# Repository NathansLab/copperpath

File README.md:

# copperpath

Rule-aware routability check, placement helper and grid router for **already-placed KiCad boards**,
written in Rust (parallel with rayon). It reads the board, the net classes (`.kicad_pro`) and the
custom rules (`.kicad_dru`) directly, routes signal nets with exact clearance checks and writes the
result back as ordinary KiCad tracks and vias.

**Status: research prototype.** Tested on KiCad 10 boards (2, 4 and 6 copper layers). Expect
rough edges; see [Limitations](#limitations) and [ROADMAP.md](ROADMAP.md).

At a glance (every command takes `--json`; times on 4 cores):

| | |
|---|---|
| **One-shot routing** | `autoroute`: planes, fanout, signals, pours, thermal fixes and a DRC gate in one call; 2 of 8 PCBench boards fully routed, the others with 1-11 % of their connections left open ([benchmark](#benchmark-pcbench)) |
| **Routing intents per net** | `low_r`, `wide`, `low_l`, `short`, `few_vias`, `quiet`, `first`, `outer`, `z:OHM` (impedance width from the stackup), `pair` (differential pairs); from `--prio`, the project file or the net class name ([intents](#routing-intents-per-net---prio)) |
| **Length matching** | `tune --match 'D[0-7]'`: exact-length accordion meanders, clearance-checked |
| **Native DRC** | the copper checks of `kicad-cli pcb drc` with KiCad's semantics in 7-105 ms instead of 0.7-1.8 s ([DRC](#native-drc-drc)) |
| **For agents** | `status` (overview, suggested intents, next commands) in milliseconds, `explain` (why a net is open), `ripup` + `route --nets` (redo a net in about a second), `netinfo` (R, L, Z0, coupling, bus skew); [a recorded session](docs/agent-session.md) |

## Numbered net compatibility

KiCad 6–9 boards use a numbered net table; KiCad 10 references nets by name. CopperPath now resolves numbered pads, tracks, vias and zones to their real names, validates code/name consistency, and preserves the input net-reference format when routing, applying deltas or creating planes. This fixes routed KiCad-9 output containing invalid quoted numeric net references. Named numeric strings on KiCad-10 boards remain names. Complete compatibility with every older KiCad feature is not implied.

The agentic-eda divider integration independently checks the routed output with KiCad 9 DRC and exports Gerbers; `tests/numbered_nets.rs` covers non-contiguous codes, malformed tables, delta application and roundtrip routing. Existing named-net tests remain required.

## Build

Requires a recent stable Rust toolchain (developed with 1.95).

```bash
cargo build --release          # binary: target/release/copperpath
cargo test --release           # unit tests + routing of the demo board
```

Optional: KiCad 10's `kicad-cli` for the DRC comparison (`route --drc`). It is found via
`--kicad-cli PATH`, else `$KICAD_CLI`, else `kicad-cli` on the `PATH`.

## Quickstart (demo board)

`examples/demo/` holds a small synthetic 4-layer board (25 parts, 24 nets, one rule area, two net
classes, three custom rules), placed but not routed.

```bash
B=target/release/copperpath
$B route --pcb examples/demo/demo.kicad_pcb --out out/demo_routed.kicad_pcb --threads 4
#   [route] 24 nets, 50 connections: 189 segments (604 mm), 29 vias ... 0 opens
$B route --pcb examples/demo/demo.kicad_pcb --out out/demo_routed.kicad_pcb --drc --json
#   {"ok": true, "opens": 0, "vias": 29, "drc": {"new_errors": 0, ...}, ...}
$B check --pcb examples/demo/demo.kicad_pcb --out out/check     # routability report + PNG maps
$B hints --pcb examples/demo/demo.kicad_pcb                      # placement hints
```

Open `out/demo_routed.kicad_pcb` in KiCad. The input board is never modified.

## Commands

All commands take `--pcb BOARD.kicad_pcb`. Common options:

| option | meaning |
|---|---|
| `--cfg config.json` | optional board configuration (see `examples/config.json`) |
| `--board NAME` | entry under `"boards"` in the config (default: the first) |
| `--pro F` / `--dru F` | project / custom rules file (default: next to the board) |
| `--threads N` | worker threads (default: all cores) |
| `--json` | one JSON result object on stdout; logs stay on stderr |
| `--version` | version and git hash |

| command | job |
|---|---|
| `route [--region x0,y0,x1,y1] [--nets PATTERNS] --out OUT.kicad_pcb [--delta-json DELTA.json] [--drc]` | Detailed router (below). Routes every routable net whose pads lie in the region (default: whole board). Appends unlocked tracks/vias to a copy and writes `OUT_route.json`; `--delta-json` writes the added/removed items in nm for the KiCad IPC API ([schema](#change-set-for-the-kicad-ipc-api---delta-json)). `--drc` runs `kicad-cli` on input and output and reports the new violations. |
| `check [--out DIR] [--res 0.25] [--tile 1.0] [--copper locked\|all] [--crop x0,y0,x1,y1 --crop-class C]` | Routability report: via-site maps per net class, region analysis per schematic sheet, what-if ablation (without rule areas, via keepouts, locked copper), global route with congestion per tile and layer, hotspot list. Writes `report.json`, `groute.json`, `congestion.json` and PNG maps. |
| `place --zones zones.json [--init keep\|schematic\|both] [--moves N] [--starts K] [--out DIR]` | Parallel simulated-annealing placement of the movable parts inside zones (see `examples/zones.json`). Writes `place.json`; apply it to a copy with `scripts/apply_place.py`. |
| `tune --match REGEX [--target MM] [--gap MM] [--amax 1] --out OUT` | Length matching: accordion meanders on straight tracks bring every matching net to the target length (default: the longest of them); each bump adds twice its amplitude, the last one the remainder, so the target is met exactly; every new segment keeps the clearances to other nets' copper, holes, rule areas and the board edge. `--json`: length before/after and meanders per net. |
| `thermals --out OUT` | Refills the zones natively and gives every starved thermal pad (fewer than 2 resolved spokes, counted as kicad-cli 10 does: spokes into isolated islands only count when nothing else does, a track from the pad into the fill counts) a short legal stub track into its zone's fill, preferring fill connected to other items. `--json`: starved pads and stubs added. |
| `ripup --nets PATS [--region BOX] [--locked] --out OUT` | Removes the unlocked tracks and vias of the matching nets (with `--locked` the locked ones too), optionally only those touching a region; `--json` lists what was removed per net. With `route --nets` an agent redoes single nets in well under a second. |
| `status [--refill-zones]` | One-call overview for agents, in milliseconds: copper stack, net classes, zones with their selection key, plane nets and candidates, opens per net, native DRC by type, routing intents suggested from the net names (`suggested_prio`: supply rails `wide`, clocks `low_l`, RF `z:50+outer`, analog `quiet`), and the next commands to run (`--json`: `next`). |
| `netinfo [--nets] [--cu-um 35]` | Length, vias, track width and estimated DC resistance (mΩ) and inductance (nH) per net, in milliseconds. See [Routing intents](#routing-intents-per-net---prio). |
| `drc [--refill-zones] [--out report.json]` | Native copper DRC with KiCad's rule names in milliseconds. See [Native DRC](#native-drc-drc). |
| `opens [--region] [--nets] [--max-islands 50]` | Unconnected connections per net, counted from all copper including saved zone fills (no 499-item cap as in kicad-cli). Nets named in `--nets` are counted even if they are plane nets. `--json` lists the islands of each open net (pads per copper component, largest first). |
| `hints [--region] [--nets] [--tol 1.0]` | Pad pairs of a net that are *almost* in one row or column (offset 0.02..tol mm). Each forces a jog between two straight pad exits; align the pads before routing. |
| `stitch --net GND --zones REGEX --plane REGEX [--grid G] --out OUT.kicad_pcb` | Stitching vias for a plane net from the saved zone fills: one via in every fill island of the `--zones` zones (zone name, full match; an unnamed zone matches as `NET@LAYER`, e.g. `GND@In1.Cu`) that has no via or plated hole of the net, optionally a via grid of pitch G per island. A via must lie on a fill of a `--plane` zone of the same net (fully on its copper), keep the DRU/net-class clearance to every other net on every layer (outer layers incl. creepage, last matching rule wins) plus `--margin` (0.05), 0.2 mm to every pad, the hole and edge rules, and stay out of no-via rule areas. Unlocked zones of other nets are ignored (they refill around the via), locked ones are copper. Options: `--via D,DRILL` (default: the net class via), `--min-clr` (floor on the clearance to other nets), `--min-area` (0.3 mm²), `--base B.kicad_pcb` (write the vias into this board instead of the input, e.g. the unfilled original). `--json` lists the vias, the islands without a legal spot (with the nearest blockers of a via there) and the rejection causes. |
| `fanout --net GND --plane REGEX [--reach 6] --out OUT.kicad_pcb` | Connects every open island of a plane net (a copper island with pads that touches no fill of a `--plane` zone) with one short track and a via onto the plane: grid search (0.05 mm, 8 directions) from an SMD pad of the island on its outer layer to the nearest legal via spot within `--reach` mm of track. Track legality as in the router (DRU/net-class clearance incl. outer-layer creepage, rule areas, mask apertures, edge); via legality as in `stitch`. Width: `--width` or the net class / DRU width, inside the pad's own courtyard the width of a DRU `track_width` rule with `A.intersectsCourtyard('REF')` (neck-down). Pads whose own cells are already too close to other copper (in-package creepage) are skipped. Options: `--via D,DRILL`, `--margin`, `--min-clr`, `--islands opens.json` (only islands listed by `opens --json`), `--base`. `--json` lists per island the pad used, track length and via, or why each pad failed and the nearest blockers (`net`, `kind`, `fp`, `layer`, `dist_mm`, `need_mm`, `locked`, `at`: the copper closest to violating its clearance, i.e. what to move). The search runs in 8 directions, so 45-degree tracks to a via spot are tried as well. |
| `nudge (--parts R5,R7 \| --spec moves.json \| --auto) [--range 1] [--step 0.05] [--rots 0,90] --out OUT.kicad_pcb [--dry-run]` | Local placement optimisation by real routing: moves a few small parts (translation on a grid, rotation about the footprint origin, side kept) until their nets route, see [Nudge](#nudge-local-placement-by-real-routing). Writes the moved footprints and the new copper to a copy and `OUT_nudge.json`. |
| `render [--roi x0,y0,x1,y1] --out roi.png` | PNG of a board region for AI agents and humans, native rasteriser (about 0.05 s per image). See [Rendering](#rendering-render). |
| `autoroute --out OUT.kicad_pcb [--time 600] [--planes In1.Cu=GND]` | Placed board to routed board in one command: plane zones, plane fanout, signal routing, rip-up of blockers, stitching, quality gate. See [One-shot routing](#one-shot-routing-autoroute). |
| `explain [--net N] [--pad REF.PIN] [--explain-img DIR]` | Why connections are open: reason, widest corridor, blockers, ROI image. See [Explaining failures](#explaining-failures-explain). |
| `plane list\|report\|fill\|create\|adjust` | Plane zones: detection, native zone filler, report (islands, unconnected pads, necks, stitching coverage), zone creation with HV cut-back, grow/merge. See [Planes](#planes-plane). |
| `pads` | Pad world positions, sizes and nets (tab separated). |
| `netclass` | net → net class table (tab separated). |

`--nets` takes comma-separated wildcards (`*`, `?`), e.g. `--nets "/Driver/*,+5V"`.

### Route options

| option | default | meaning |
|---|---|---|
| `--res` | 0.05 | grid resolution in mm; `auto`: 0.1 mm when every routed net has at least 0.2 mm clearance and width and no pad pitch is under 0.5 mm (4x fewer cells) |
| `--via-cost` | 30 | via cost (in grid steps) |
| `--bend-cost` / `--bend90` | 4 / 1.4 | cost of a 45° bend / factor for 90° bends |
| `--hweight` | 1.02 | A\* heuristic weight (>1: faster, less optimal) |
| `--max-expand` | 4e6 | node budget per search (at least half the nodes of the net's window) |
| `--iters` | 25 | negotiation iterations |
| `--job-margin` | 6 | per-net search window margin in mm |
| `--time-limit S` | | stop negotiating in time and write the best iteration so far (conflicting nets ripped and rerouted, or left as failed); SIGTERM / Ctrl+C (Ctrl+Break on Windows) do the same at once. `--json` reports `stopped` (`time-limit`, `signal`, `cancel`) and `hotspots` (net, conflict cells, location, layer) |
| `--cancel-file PATH` | | stop like `--time-limit` as soon as this file exists (checked once per second); a cancel path that also works on Windows, where a GUI can only kill the process otherwise. The file should not exist at the start |
| `--cancel-on-stdin-eof` | | stop like `--time-limit` when stdin is closed, e.g. because the calling plugin or KiCad ended |
| `--progress-json` | | machine-readable progress on stderr, one JSON object per line ([events](#progress-events---progress-json)) |
| `--stall-iters` | 3 | stop negotiating after this many iterations without fewer conflict cells, then rip up and reroute the conflicting nets |
| `--stall-gain` | 0 | an iteration counts as progress only if it cuts the best conflict count by this fraction (0.1 = 10 %); stops plateaus early |
| `--no-fallback` | off | skip the cleanup fallback ladder (two more full routes when the exact check drops nets); the dropped nets stay open and are reported |
| `--par-nets` | 1 | 1 = nets whose windows cannot interact route in parallel (same result as serial); N > 1 = blocks of N nets against one snapshot (experimental) |
| `--par-conn` | 1 | experimental: parallel connection searches inside a multi-pin net (0 = all threads); slower on the benchmark boards so far |
| `--no-stubs` / `--no-clean` | | disable straight pad exits / the cleanup |
| `--stub-ext` / `--stub-ext-long` | 0.6 / 0.6 | exit stub length beyond the pad (mm) |
| `--own-pad-cost` / `--stub-side-cost` | 40 / 20 | cost of crossing own pads / of side exits on long pads |
| `--yield-pours PATTERNS` | | locked pours (zone name wildcards) that do not block (KiCad refills them); also `yield_pours` in the config |
| `--ignore-unlocked` | | the router does not see unlocked tracks, vias and zones of the input, but they stay in the output (route never removes copper), so new copper can overlap or short them. Only for experiments where the old copper is deleted afterwards; rip up instead (see below) |
| `--reroute-blockers` | | after routing, for each net still open: a coarse search (0.1 mm, all layers) in which unlocked tracks/vias of other nets are passable at a high cost finds the cheapest corridor; the unlocked copper on it is ripped and the net is routed again together with the ripped nets (negotiated as usual). A try is kept only if the net gets fewer opens and no ripped net and no other net ends up with more opens; otherwise it is rolled back. Locked copper, pads, rule areas and the edge are never moved. `--json`: `reroute` = per net `ripped_nets`, `ripped_items`, `accepted`, opens before/after, `reason` |
| `--max-ripped N` / `--max-targets N` | 3 / 10 | blocking nets ripped per try / open nets tried |
| `--dbg-net NAME` | | verbose trace of one net |

## Rendering (`render`)

One PNG of a region with every copper layer colour-coded and semi-transparent (KiCad colours,
B.Cu at the bottom, F.Cu on top), so an AI agent can *look* at a placement or routing problem
instead of reading coordinates. Native Rust, no Python or matplotlib.

```bash
B=target/release/copperpath
# region around a part, labels, ratsnest of the open connections, DRC markers
$B render --pcb board.kicad_pcb --roi 110,105,135,125 --labels --opens --drc drc.json --out roi.png
# one small image per copper layer (small multiples)
$B render --pcb board.kicad_pcb --per-layer --layers F,In1,In2,B --labels --out sheet.png
# one net highlighted, all other copper grey
$B render --pcb board.kicad_pcb --hl-net GND --fills --out gnd.png
```

| option | default | meaning |
|---|---|---|
| `--roi x0,y0,x1,y1` | board + 1 mm | region in board mm |
| `--px N` | 1200 | image width in pixels (height from the aspect ratio) |
| `--layers F,In1,..,B` | all | copper layers to draw (`F.Cu` style names work too) |
| `--nets REGEX` / `--hl-net NAME` | | only these nets / this net in colour, everything else grey |
| `--fills` | off | saved zone fills (`filled_polygon`), lighter than tracks |
| `--labels` | off | `REF.PIN` and net name on every pad in the region (largest pads first, never overlapping; a label that does not fit is moved beside the pad or dropped), net names on long tracks |
| `--opens` | off | ratsnest: one white line per open connection (minimum spanning tree over the copper islands of each net, closest pad pair) |
| `--drc FILE` | | markers from a `kicad-cli pcb drc --format json` report: red X for errors, yellow for warnings, dashed line for unconnected items |
| `--courtyards` | off | courtyard outlines |
| `--halo-min D` | 1.0 | nets whose outer-layer clearance (incl. creepage) to another net in the region is at least D mm get a hatched halo of that width (HV creepage zones); 0 = off |
| `--per-layer` | off | one tile per layer in a grid |

Always drawn: board outline, rule areas (orange hatch), vias and drill holes, a millimetre grid
with coordinates along the top and left edge, a scale bar and a legend. `--json` returns the
image size, the region, `px_per_mm`, the number of labels and the open connections in the region
(`ratsnest`: net, both pads, end points, length).

## Planes (`plane`)

Plane nets (GND, supply rails) get zones instead of tracks. `plane` creates and edits those
zones, fills them natively and reports how well they connect, without `kicad-cli`.

```bash
B=target/release/copperpath
$B plane list --pcb board.kicad_pcb                       # plane/pour nets and power-like candidates
$B plane create --pcb board.kicad_pcb --net GND --layer In1.Cu --out step1.kicad_pcb
$B plane create --pcb board.kicad_pcb --net +3V3 --layer In2.Cu --region 100,100,140,150 \
   --hv "HV_.*" --creepage 3 --out step1.kicad_pcb       # cut back 3 mm from the HV nets
$B plane adjust --pcb step1.kicad_pcb --zone "cp_plane_*" --grow max --merge --out step2.kicad_pcb
$B plane report --pcb step2.kicad_pcb --net GND --json --png gnd.png
$B plane fill --pcb step2.kicad_pcb --out filled.kicad_pcb  # write native fills (filled_polygon)
```

| subcommand | job |
|---|---|
| `list [--min-pads 4]` | nets with copper zones (`plane`: a zone on an inner layer, `pour`: any zone) and power-like nets (`GND*`, `+*`, `VCC*`, `VDD*`, `VBAT*`, ...) with at least N pads and no zone (`candidate`), with net class, pad count and zones. |
| `create --net N --layer L [--region box] [--hv REGEX --creepage D] [--priority P] [--name NAME] --out F` | one zone of net N on layer L over the board (or the region): the free area of the layer, i.e. inside the board, outside pour keep-outs, rule clearance (+ `--margin`) away from zones of other nets, and `--creepage` mm away from all copper of the `--hv` nets on that layer. Parts narrower than `--min-neck` (1.0 mm) and outlines under `--min-area` (4 mm²) are dropped. The outline is cut back where HV copper reaches it; HV copper inside the plane gets a pour keep-out rule area (`NAME_hvK`, copper pour not allowed, tracks and vias allowed). Name `cp_plane_<net>_<layer>`; a re-run replaces its own zone and keep-outs. Clearance from the net class, `--min-width` (0.25) as minimum thickness, thermal reliefs; KiCad fills it. |
| `adjust --zone NAME [--grow D\|max] [--hv REGEX --creepage D] [--merge] --out F` | edits existing zones (name wildcards): grow the outline by up to D mm (`max`: the whole free area connected to it) into the free area as above, cut it back from HV copper, `--merge` joins the selected zones of one net and layer set into one outline. Only the polygon changes; every other zone setting is kept, saved fills are dropped. |
| `report [--net N] [--stitch-radius 5] [--necks 5] [--png F [--roi] [--labels]]` | native fill of every zone of the net (default: all nets with zones), then per zone and layer: outline and fill area, lost area (%), islands, isolated islands (no copper of the net: KiCad removes them), connected islands without a via, share of the largest island, stitching coverage (fill within `--stitch-radius` mm of a via or plated hole, %), narrowest neck; per net: copper components through all copper (tracks, vias, pads, native fills), unconnected pads (not in the largest component), the narrowest necks with position. `--png` renders the net with its native fill, ratsnest and the necks as markers. |
| `fill [--net N] --out F` | writes the native fill as `filled_polygon` into a copy (fractured polygons like KiCad's). |

Native filler: raster of the zone's layer (`--fill-res`, 0.1 mm), KiCad's recipe: the area where
a disk of half the minimum width (`--min-width`, 0.25 mm) fits (outline, board edge clearance,
clearance + half width to foreign copper, holes, pour keep-outs, zones of other nets with a higher
priority) grown again by half the width. Pads of the net connect solidly (thermal spokes are not
modelled), isolated islands are dropped. On the demo board with a GND plane on In2 the filled
area matches KiCad's within 0.2 %; 0.05 s per zone layer. A neck is where two parts of an island
that both hold copper of the net meet (widest-path tree over the distance to the fill edge).

`--native-fill` on `fanout`, `stitch`, `opens` and `render` fills all copper zones natively first
(instead of the saved fills), so the plane loop needs no kicad-cli refill.

## One-shot routing (`autoroute`)

```bash
$B autoroute --pcb placed.kicad_pcb --planes In1.Cu=GND,In4.Cu=+3V3 --time 600 --drc    --explain-img why/ --out routed.kicad_pcb --json
```

Stages (each writes its board to `OUT_stages/`, the input is never modified):

1. **planes**: `--planes LAYER=NET[+NET],...` creates the missing plane zones (`plane create`).
   Plane nets = the nets of `--plane-nets A,B`, of `--planes` and every net with a copper zone
   on an inner layer; they are not routed as signals. Nets with outer pours only (two-layer
   boards) are pour nets, see stage 3c.
2. **fanout**: every open island of each plane net gets a track + via onto its plane
   (`fanout --native-fill --plane-only`; the plane = its zones on inner layers; outer pours of
   the net do not join pads here, so tracks routed later cannot strand a pad cut off a pour).
3. **route**: the negotiated router for all other nets with `--time-limit` = the time left minus
   a reserve, plus `--reroute-blockers` (off with `--no-reroute`). Signal tracks stay off inner
   layers whose plane zones cover at least half the board (`--signal-layers auto`, the default;
   `all` or a layer list to override); vias still pass through the planes.
   `--second-pass` retries the nets left open with `--job-margin 20 --max-expand 2e7` in the
   time left.
3c. **pours**: the pour nets are routed after the signals: the zones are filled natively and
   the router only joins what the fill leaves apart, starting on the fill (no signal is
   ripped); new tracks can cut another pour, so fill and route repeat up to 3 times. Plane
   nets with pads the plane and the fanout could not join (dense through-hole pins between
   which the plane cannot pour) are routed here too, on the signal layers.
3e. **polish**: when a quarter of the budget is left (small boards finish early), the nets
   still open get a rip-up-and-reroute round on the filled board (up to 20 targets); the result
   is kept only when the board has fewer opens (rf_siggen 16 -> 14, rxadc_14 5 -> 4; off with
   `--no-polish`).
3d. **thermals**: pads whose thermal relief resolves to fewer than 2 spokes (`starved_thermal`
   in kicad-cli) get a short stub track from the pad centre into connected fill of their zone,
   which kicad-cli counts as a spoke (`thermals`; off with `--no-thermals`). On the routed
   sizif128 board: kicad-cli `starved_thermal` 17 -> 7, no new violations.
4. **stitch**: stitching vias for outer pours of the plane nets onto their inner planes
   (`--stitch-grid G` adds a grid; off with `--no-stitch`).
5. **gate**: opens of every net counted with native fills; with `--drc` KiCad DRC of the result
   against the input; if a stage added DRC errors, the latest stage without new errors is
   written, and if none is clean nothing is written (exit 1, `--allow-drc` writes anyway).

`--json`: `opens_before`, `opens`, `open_nets`, `plane_nets`, `within_budget` and per stage
`s`, `opens`, `note`, `out` and details (fanout islands, route `open_nets`, DRC deltas). With
`--explain` / `--explain-img DIR` the open connections of the result are explained (see
[Explaining failures](#explaining-failures-explain)). Routed copper that fails the exact
clearance check is never written: the failing segments and whatever then dangles are removed,
the rest of the net stays, and the connection is left open (`aes.exact_dropped` counts the nets).

Synthetic stress board (`scripts/make_stress.py --parts 800`: 798 footprints, 6 layers, 515
signal nets, GND/+3V3 zones on In1/In4; 4 cores, 8 GB): 1331 to 174 opens in 75 s (fanout 3 s,
route 70 s). Before skipping the fallback ladder for pure search failures (#54) the route stage
took 217 s. The 134 signal opens left are router search failures where `explain` finds a legal
corridor (#87), the 40 plane opens are pads whose fanout found no via spot.

Demo board, `--planes In1.Cu=GND`: 50 to 0 opens in 8 s (gate with KiCad DRC +16 s, 0 new
errors; KiCad warns about dangling GND vias until the plane is refilled).

## Routing intents per net (`--prio`)

`route` and `autoroute` take a routing intent per net (`--prio NET=PROFILE,...`, wildcards, or
`net_prio` in the config). It scales the router's costs for that net and its track width, and
nets marked `first` are routed before the others:

| profile | effect | use for |
|---|---|---|
| `low_r` | twice the class width (pads keep the neck-down), vias cost 2x, first | high current; costs completion on dense boards (icehat, `--time 10`: 26 instead of 18 open), where `wide` is the gentler choice |
| `low_l` | vias cost 3x, bends and the wrong layer direction cheap (direct path), first | clocks, gate drives, decoupling loops |
| `short` | bends and the wrong layer direction cheap | sense lines, short analog paths |
| `few_vias` | vias cost 4x | signals that should stay on one layer |
| `wide` | 1.5x the class width | supply rails, moderate current (what `status` suggests for rails) |
| `quiet` | cells within 0.5 mm beyond the clearance of other nets' copper (fixed and routed) cost more | sensitive analog, clocks next to aggressors |
| `first` | routed before the other nets | the nets that matter most |
| `pair` | differential pair: the negative net (`_N`, `-`, `DM`) follows the positive one (`_P`, `+`, `DP`, routed first) at the class `diff_pair_gap` (else the clearance), both at `diff_pair_width` if set; the follower skips the pull-tight | USB, LVDS, MIPI: `USB_D*=pair` |
| `outer` | tracks only on F.Cu and B.Cu (vias still pass the inner layers) | with `z:` so the width holds everywhere, nets to probe or rework |
| `z:OHM` | track width for that single-ended impedance on the outer layers, from the board stackup (microstrip, Hammerstad-Jensen; without a stackup: FR4 4.5, 35 µm, 0.2 mm prepreg on multilayer boards, 1.51 mm on two layers) | RF, USB/LVDS lines, clocks: `RF_OUT=z:50` |
| `via:X` `bend:X` `dir:X` `width:X` `iso:X` | the multipliers themselves, `iso` the soft spacing in mm | fine tuning |

Pairs whose names do not mark the polarity (`Net-(J1-Pad3)`) are named explicitly:
`--pairs 'POS=NEG;POS2=NEG2'` or `"pairs": [["POS", "NEG"]]` in the config or the project's
`copperpath` block; they need no `pair` intent.

A differential pair without and with `pair` (`USB_D*=pair`; `netinfo --near 0.4`: USB_D- runs
within 0.4 mm of USB_D+ for 1.7 mm without, 28 mm of its 34 mm with the intent; DRC clean):

`tune --match 'PWM_.*|ADC[12]'` then matches such a group to its longest net (demo: skew
4.97 mm -> 0, DRC clean; left before, right after):

`netinfo --match 'D[0-7];A[0-9]+'` adds the length skew per group of nets (shortest, longest,
`skew_mm`) for buses that need length matching. `netinfo` reports `z0_ohm`, the microstrip impedance of a net's narrowest outer-layer track
(demo, `CLK=z:50`: 0.341 mm, 50.0 Ω). `netinfo` also reports `coupled_mm`, the track length running closer than `--near` (0.5 mm, edge
to edge) to another net's copper on the same layer: on the demo, `CLK=quiet` cuts it from 11.2 to
0.1 mm at the same length.

Profiles combine with `+` (`CLK=low_l+wide`). A key `class:PATTERN` applies to the nets of the
matching net classes (`--prio 'class:Power=low_r'`). The intents can live in the KiCad project
next to its net classes, as a `copperpath` block in the `.kicad_pro` (KiCad keeps unknown keys):

```json
"copperpath": { "net_prio": { "class:Power": "low_r", "CLK*": "low_l", "SW": { "via": 3, "width": 2 } } }
```

The net class itself can carry the intent: a KiCad net class named after a profile (`quiet`,
`low_l+wide`) or ending with one in brackets (`Power [low_r]`) gives its nets that intent, so it
shows up in KiCad's net class list without extra configuration.

Order: `--prio` first, then `net_prio` of `--cfg`, then the project block, then the net class
name; the first match wins. `netinfo` reports the result per net: length, vias,
width and rough DC resistance (copper 35 µm, `--cu-um`) and partial inductance (Grover formula
for the total length plus about 1.3 nH per 1.6 mm via). Demo board, `route` without and with
`--prio '+5V=low_r,CLK=low_l,ADC1=few_vias'` (both DRC-clean):

| net | without | with |
|---|---|---|
| +5V (`low_r`) | 0.4 mm, 51.2 mm, 64.5 mΩ | 0.8 mm, 50.4 mm, **32.6 mΩ** |
| CLK (`low_l`) | 22.1 mm, 2 vias, 27.1 nH | 22.4 mm, **0 vias, 24.9 nH** |
| ADC1 (`few_vias`) | 17.8 mm, 3 vias | 18.4 mm, **0 vias** |

Left without, right with `--prio '+5V=low_r,CLK=low_l,ADC1=few_vias'` (`render --nets
'\+5V|CLK|ADC1' --labels`: only these nets' copper, F.Cu red, B.Cu blue).

## Native DRC (`drc`)

```bash
$B drc --pcb routed.kicad_pcb --refill-zones --out report.json --json
```

The copper checks of `kicad-cli pcb drc`, on copperpath's model: `clearance`, `shorting_items`,
`tracks_crossing`, `hole_clearance`, `hole_to_hole`, `copper_edge_clearance`, `track_width`,
`via_diameter`, `annular_width`, `drill_out_of_range`, `starved_thermal` (with `--refill-zones`, resolved as kicad-cli 10: spokes per fill polygon,
spokes into single-connection islands ignored while the pad has another spoke or a track into
the fill) and
`unconnected_items`, with KiCad's semantics (net classes, DRU and pad clearances, the 0.0005 mm
epsilon, one collision per net pair, collisions only between nets with pads). `--refill-zones`
fills the zones natively first (like kicad-cli's flag, with thermal reliefs), otherwise the
saved fills count. `--out` writes a report in kicad-cli's JSON layout.

Checked against kicad-cli 10.0.7 on six routed PCBench boards (see the benchmark below) and on
synthetic boards:

- with the zone fills saved by KiCad: the same violations per type and the same unconnected
  items per net, in 10-40 ms instead of 0.8-0.9 s per board;
- with `--refill-zones` (native filler, 0.05 mm raster by default, `--fill-res`): the same
  copper violations, unconnected items within 1-2 of kicad-cli's and `starved_thermal` within 2
  (the filler rasterises necks that are exactly the minimum width), 0.1-1.2 s instead of 1-2 s.

`route`, `nudge` and `autoroute` take `--drc native` for their DRC gate: the same comparison
against the input as `--drc` (kicad-cli), with the input's rules for both boards, in
milliseconds. Pads with the same number in one footprint count as one terminal (as in KiCad).
Board setup minimums missing from the project take KiCad's defaults (0.5 mm via, 0.1 mm annular
ring, 0.3 mm hole), for the router as well. Not covered: silk, courtyard, solder mask, footprint
library checks, and copper islands without pads (KiCad counts floating
tracks as unconnected items). Use it as the fast check while iterating and kicad-cli for
sign-off.

## Explaining failures (`explain`)

Every failure comes with a one-line reason for humans and agents, and optionally a small image.
`--explain` adds them to the JSON of `route`, `fanout`, `stitch` and `plane report`;
`--explain-img DIR` also writes one ROI image per failure (the net highlighted, its ratsnest,
labels, rule areas, HV halos, the bottleneck as a red marker and the blockers as yellow markers,
scale bar). `copperpath explain` analyses the open connections of one net (or one pad) directly.

```bash
$B explain --pcb routed.kicad_pcb --net /Driver/PWM_A --pad U3.7 --explain-img why/ --json
$B route --pcb board.kicad_pcb --out routed.kicad_pcb --explain-img why/ --json
$B fanout --pcb board.kicad_pcb --net GND --plane "GND_In.*" --native-fill --explain --out f.kicad_pcb
```

For an open connection (the two closest pads of two copper islands of the net) the legal
track-centre area is rasterised in a window around both pads (all allowed layers, vias where one
fits; clearances from the DRU/net classes incl. creepage, rule areas, mask apertures, board edge):

| `kind` | meaning |
|---|---|
| `congestion` | a corridor at the net's minimum width exists: the router ran out of iterations or budget (try `--reroute-blockers`, `--iters`, a region route) |
| `routed-copper` | only unlocked tracks/vias of other nets block it; `rip_nets` lists the rip-up candidates |
| `neck-down` | only the minimum width gets through, but the router allows it within 1.5 mm of the own pads only; `at` is where the net width does not fit |
| `too-narrow` | fixed obstacles leave at most `corridor_mm` of track (< `need_mm`); `at`/`layer` is the bottleneck, `blockers` what to move |
| `enclosed` | no legal path even for a zero-width track; `at` is the reachable point closest to the target |

Example reason: `widest free corridor fits a 0.05 mm track < 0.20 mm needed at (19.62, 14.78)
F.Cu: blocked by locked track SIG on F.Cu (0.20 mm away, needs 0.20)`. Options: `--explain-max`
(20), `--explain-px` (900). About 0.05 s per connection including the image.

### Existing copper, "route the rest" and rip-up

`route` never removes or moves existing copper: every track, via and zone of the input stays in
the output with its UUID, and the delta's `remove` list is empty. Existing tracks and vias of a
net count as connectivity for that net and as obstacles for all other nets, locked or not
(unlocked zones yield, KiCad refills them). So routing
again after manual work only adds the missing connections ("route the rest"); a separate
`--lock-all-existing` option is not needed, it is the default. New copper is written unlocked
with fresh UUIDs (seeded from the input board, so a second run never repeats the first run's
UUIDs).

To redo nets, rip them up first: delete their unlocked tracks and vias (in KiCad, or with the
plugin's **Rip up selected nets**), then route them with `--nets`.

## How routing works

- **Model.** Grid of 0.05 mm cells on every copper layer of the board, 8 directions plus through
  vias. Legality is exact at cell centres: a track centre may sit in a cell when its half width
  plus the clearance from the net-pair matrix (net classes + DRU rules, outer/inner layer
  conditions, hole clearances, rule areas, board edge) keeps it off every foreign object; touching
  the clearance exactly is legal, as in KiCad's DRC. Solder mask apertures on the outer layers
  (F/B.Mask graphics, pad mask expansions from the pad, footprint or `pad_to_mask_clearance`) admit
  only the nets of the pads and locked zones inside them, so no copper of another net is exposed
  next to a pad (KiCad `solder_mask_bridge`). Tracks use the DRU/net-class optimal width; within
  1.5 mm of own pads the minimum width is allowed (neck-down for fine pitch). The grid is shifted
  by less than one cell so that the axes of the tightest pin rows lie on cell centres (a 0.2 mm
  track between 0.2 mm pads at 0.4 mm pitch fits only exactly on the pad axis).
- **Search.** Windowed multi-target A\* per net; nets are routed in parallel per iteration. A
  connection starts or ends at a pad (through its exit stub) or on any existing track or via of
  the same copper component, so a boxed-in pad still joins through its own via.
- **Negotiation.** PathFinder-style congestion costs (present × occupancy + history), stall
  detection, then rip-up of the most conflicted nets and a hard reroute.
- **Verification.** All routed copper is checked exactly against fixed objects and other nets
  before writing; a failed check is reported (`aes.exact_fail`), never silently written.

### Aesthetics rules (on by default)

- **Straight pad exits.** Each pad gets precomputed exit stubs per layer and pad axis, running from
  the pad centre along the axis to half extent + 0.6 mm. Long pads (aspect ≥ 1.2) exit along the
  long axis whenever that is legal. Where no full stub fits, a short stub (0.12–0.4 mm beyond the
  pad) is used and counted (`aes.short_stubs`).
- **45° only.** Tracks are octilinear; no turns sharper than 90°; 45° bends are cheaper than 90°.
  A final polish replaces slightly off-angle segments by small axis jogs (`aes.axis_jogs`).
- **Exact cleanup.** Stub alignment, octilinear pull-tight with 1–3 segment links, jog merge,
  stub-end and junction sliding (never into pads), via slide onto the stub axis, 45° mitering of
  90° corners, removal of tiny junction legs. Every change is re-checked against the rules and the
  other nets, so the cleanup cannot add DRC errors. Kept 90° corners are reported by cause
  (`aes.kept90_by_cause`).
- **Fallback ladder.** If the cleanup costs completeness (a net loses a connection), the router
  reruns without sliding (`no-slide`), then without cleanup (`no-clean`). The level used is in
  `aes.cleanup_level`.

## Nudge: local placement by real routing

A pad that the router cannot reach is often fixed by moving a resistor half a millimetre or turning
it. `nudge` searches such moves and judges every candidate by routing it for real:

```sh
# move R5 and C7 by up to 1 mm on a 0.05 mm grid, also try them turned by 90 degrees
copperpath nudge --pcb board.kicad_pcb --parts R5,C7 --range 1 --step 0.05 --rots 0,90 \
  --out nudged.kicad_pcb --json
# only report the best moves
copperpath nudge --pcb board.kicad_pcb --parts R5 --dry-run --json
# pick the parts automatically: unlocked 2-pad SMD parts within 3 mm of an open connection
copperpath nudge --pcb board.kicad_pcb --region 40,20,60,35 --auto --auto-dist 3 --auto-max 4 \
  --out nudged.kicad_pcb
# joint moves: neighbouring small passives within 2 mm may be pushed up to 1.5 mm out of the way;
# open connections from the parts up to 40 mm away are routed too; LV signal tracks may be ripped
copperpath nudge --pcb board.kicad_pcb --parts C316 --range 2 --rots 0,90,180,270 --push 2 \
  --push-range 1.5 --reach 40 --rip-classes "LV_SIG*" --exclude-nets "GND*" --explain-img why/ --out n.kicad_pcb
# full move spec (per part ranges, rotations, keep-in polygon; see examples/nudge.json)
copperpath nudge --pcb board.kicad_pcb --spec examples/nudge.json --time-limit 30 --out nudged.kicad_pcb
```

- **Move space.** Per part an x/y offset range on a grid (`dx`, `dy`, `step`; default `--range`
  ±1 mm, `--step` 0.05 mm) and a list of rotations (`rot` absolute or `drot` relative, default
  `--rots 0`), optionally a `keepin` polygon. The side stays. Locked parts are refused unless
  `--move-locked`.
- **Hard rules.** Every candidate passes the placement checker of `place` first: pad clearance from
  the DRU/net-class matrix (outer layers incl. creepage), mounting-hole keepouts, via-to-pad gap,
  courtyard overlap, board edge clearance, footprint rule areas and the keep-in. A candidate may
  not have more violations than the start placement.
- **Real routing.** The nets to route are the nets of the movable parts plus the nets open in the
  region (or `--nets`). Their unlocked tracks and vias inside the region are ripped once
  (`--rip region`; `attached` rips only the copper connected to the movable parts, `none` keeps
  everything), then every candidate is routed by the detailed router inside the region (default:
  the parts' move envelope + `--margin` 2 mm).
- **Joint moves.** With several parts, candidates also shift all scanned parts together. With
  `--push R` the small passives (2 SMD pads) within R mm of a part's move envelope join as push
  parts (range `--push-range`, rotation kept): a move whose courtyard or pads collide with a
  movable part pushes that part along the move (or away after a pure rotation) until it is
  clear, up to two levels deep; the repaired candidate is checked and routed like any other
  (`pushed` counts them). Connectors, ICs and parts not allowed to move are never pushed.
- **More nets.** `--reach D`: an open connection that starts in the move envelope and ends
  within D mm is routed too (the region grows to its far end; `log[0].reach` lists them).
  `--rip-classes PATS`: unlocked copper of nets of these classes inside the region is ripped and
  rerouted as well (blocking nets). `--exclude-nets PATS`: never routed or ripped (e.g. pours).
- **Score.** Opens first, then cost = track length + `via_w` (2 mm) per via + `move_w` (2 per mm)
  × moved distance + `rot_w` (0.5) per turned part. The result is written only if it has fewer
  opens than the board as it is (`improved`).
- **Search.** A coarse scan of each part's move space (`--coarse` 9 points per axis × rotations),
  then a pattern search around the best (step halving down to the grid step), in rounds over all
  parts until nothing improves, `--time-limit` (60 s) or `--max-cands`. Candidates of a step are
  evaluated in parallel.
- **Speed.** The board is cropped once to the region plus the router's job margin (all copper of
  the routed nets stays, so their connectivity is exact). The blocker maps of everything that
  does not move are built once; a candidate only stamps the moving pads into copies of them and
  routes without the exact cleanup; the winner is routed again with the cleanup. On a 6-layer
  board with 845 footprints, two parts and three nets (32 ripped items, GND among them) a
  candidate costs about 11 ms wall time on 4 threads (≈ 0.8 ms model, 7 ms maps, 33 ms
  search per thread); 330 candidates in 4 s.

`--json` / `OUT_nudge.json`: `moves` (per part `from`/`to` as x, y, rotation and `dx`, `dy`,
`drot`), `nets` (opens before/after per net), `score` (opens, length, vias, moved mm, rotated
parts, cost), `opens_before`, `opens` (counted again on the written board), `candidates`,
`infeasible`, `infeasible_reasons` (most frequent rule hits of the rejected candidates: courtyard
overlap with which part, pad too close to which item of which net, outline, keep-in, edge, rule
area; with an example position), `pushed`, per failed net `reason` (why the router gave up) and
`components` (pins per unconnected copper component), `route_ms_per_candidate`, `search_s`, `stopped`, `log` (search phases and a time
profile), `ripped_items`, `region`, `warnings` (e.g. zones without saved fill: refill the board
first, otherwise pour connectivity is unknown and the opens are wrong). `--explain-img DIR` renders
a `render` ROI image (labels, courtyards, ratsnest) per failed net and for the top blocking
reasons and adds its path as `img`. `--drc` compares kicad-cli DRC before/after as in `route`.

Limits: no side flip; copper graphics inside a moved footprint are not moved in the routing model
(the written board moves them, KiCad keeps them local); the saved zone fills are not refilled
(run the zone filler in KiCad afterwards).

`hints` finds the placement-side cause of many ugly jogs: two pads of a net that are almost, but not
exactly, aligned. Fix those in the placement and the exits connect with one straight track.

## Board configuration

`--cfg` is optional. `examples/config.json` documents the keys: nets/classes to skip, plane nets,
footprints whose courtyard forbids vias, allowed layers per net class, preferred layer directions
for the global router, mounting-hole pattern. Keys may be per board under `"boards"`.

## Using copperpath from scripts/AI agents

Every command accepts `--json`. It then prints exactly **one JSON object** to stdout; human-readable
logs go to stderr. Exit codes: `0` success, `1` error in a known command (bad file, bad option,
kicad-cli failure), `2` unknown or missing command.

Common fields: `ok`, `command`, `version`, `threads`, `total_s`, `warnings`. On error:
`{"ok": false, "command": ..., "error": "...", "version": ...}`.

A short loop for an agent (times on the PCBench icehat board, 4 cores; a complete recorded
session with every command and its result: [docs/agent-session.md](docs/agent-session.md)):

| step | command | time |
|---|---|---|
| look | `status --json` (opens, DRC, classes, zones, `suggested_prio`, `next` commands) | 14 ms |
| route | `autoroute --out r.kicad_pcb --drc native --time 10 --json` (`--prio` with the suggested intents) | 10 s, more for dense boards (chart above) |
| check | `drc --pcb r.kicad_pcb --json`, `netinfo --json` (`--match 'D[0-7]'` for bus skew, `z0_ohm`) | 10-40 ms |
| polish | `thermals --out r2.kicad_pcb` (stubs for starved thermal reliefs; `autoroute` runs it), `tune --match 'D[0-7]'` (length matching) | 0.1-1 s |
| why open | `explain --net N --json` (reason, blockers, ROI image, `next`: the command that fixes it) | 20 ms |
| fix | `ripup --nets N`, then `route --nets N` (with `--prio` if needed), or `nudge` | 0.1-3 s |
| see | `render --opens --out r.png` | 30 ms |

`route --json` (also written to `OUT_route.json`):

```json
{
  "ok": true, "command": "route", "version": "0.1.0 (abc12345)",
  "nets": 24, "connections": 50, "opens": 0, "open_nets": [], "failed": [],
  "segments": 181, "vias": 31, "length_mm": 601.39, "routes": 43, "rips": 2,
  "search_s": 2.98, "total_s": 6.66, "threads": 4, "out": "out/demo_routed.kicad_pcb",
  "aes": { "cleanup_level": "full", "exact_fail": 0, "stub_ends": 88, "short_stubs": ["U1.3"],
           "pins_no_stub": [], "mitered": 3, "kept90_by_cause": {...}, "axis_jogs": 17, ... },
  "drc": { "violations_before": 0, "violations_after": 0, "new_violations": 0, "new_errors": 0,
           "new": [], "unconnected_before": 50, "unconnected_after": 0, "reports": [...] },
  "warnings": []
}
```

`opens --json` lists the islands of every open net; a plane net with saved fills shows its real
islands instead of one per pad:

```json
{ "opens": 2, "per_net": [ { "net": "GND", "opens": 2,
    "islands": [["R1.1", "R2.1", "U1.4"], ["R3.1", "R4.1"], ["C7.2"]] } ] }
```

Saved fills are read as KiCad wrote them (`filled_polygon`); refill first (`kicad-cli pcb drc
--refill-zones --save-board` on a copy) so they match the copper.

Plane-net loop for an agent: `plane report --net GND --json` (native fill, no kicad-cli) for the
islands, unconnected pads and necks, `fanout --native-fill` for islands of pads and tracks,
`stitch --native-fill` for the pour islands, report again. With KiCad's own fill instead: refill
a copy (`kicad-cli pcb drc --refill-zones --save-board`) and drop `--native-fill`.

Suggested agent loop: `hints` → fix placement → `route --drc --json` → accept if `ok`, `opens == 0`
and `drc.new_errors == 0`, else inspect `open_nets`, `drc.new` and `aes` and adjust nets, region
or options. Keep the input board read-only; always route into a new file.

### Change set for the KiCad IPC API (`--delta-json`)

`route --delta-json DELTA.json` writes what the run changed, so an editor plugin can apply it as
one commit (`begin_commit`, `remove_items` / `create_items`, `push_commit`) instead of reloading a
file. It works together with `--out` or instead of it (without `--out` no board file and no
`OUT_route.json` are written; `--drc` needs `--out`). `--delta-json -` prints the delta to stdout
(not together with `--json`). `--pcb -` reads the board text from stdin; give `--pro` / `--dru`
explicitly then (stdin is read to the end, so cancel with `--cancel-file`, not
`--cancel-on-stdin-eof`). The `--json` result reports `delta_json` (path) and `out` (`null` without `--out`).

```json
{"v": 1, "units": "nm",
 "remove": ["<uuid>"],
 "add": [{"type": "track", "net": "SDA", "layer": "F.Cu", "width": 150000, "start": [0, 0], "end": [0, 0]},
         {"type": "arc", "net": "SDA", "layer": "F.Cu", "width": 150000, "start": [0, 0], "mid": [0, 0], "end": [0, 0]},
         {"type": "via", "net": "GND", "at": [0, 0], "size": 600000, "drill": 300000,
          "layers": ["F.Cu", "B.Cu"], "via_type": "through"}]}
```

- All lengths and coordinates are integer nanometres (KiCad's internal unit), so nothing is lost
  to rounding; `v` is the schema version.
- `remove`: UUIDs of input items that were ripped up or replaced. `route` keeps all existing
  copper today, so the list is empty; the field is there for the incremental modes.
- `add` items carry no UUID; KiCad assigns one when the plugin creates them.
- `add`: new items in output order. The router emits `track` and through `via` items; `arc` is
  part of the schema for later cleanup steps.
- Applying the delta to the input board (`copperpath::delta::apply`) gives the same copper as
  `--out` (tested on the demo: same tracks and vias within 1 nm, same opens).

### Progress events (`--progress-json`)

`route --progress-json` writes one JSON object per line (NDJSON) to **stderr**, between the
normal log lines, for a progress bar in a GUI. Each line is written and flushed at once, so a
reader never sees a fragment; lines starting with `{` are events, all others are log. stdout and
the output files are unchanged, and without the flag no event is written.

```json
{"ev":"phase","phase":"droute","t":0.41}
{"ev":"iter","iter":0,"conflict_cells":412,"nets_conflicted":9,"nets_left":14,"nets_total":120,"iters_max":25,"eta_s":90.0,"t":12.3}
{"ev":"done","v":1,"ok":true,"routed":118,"failed":2,"opens":2,"stopped":null,"out":null,"delta_json":"delta.json","t":180.3}
```

- `t`: seconds since the start (every event).
- `phase`: `load`, `droute` (maps and negotiation), `resolve` (rip-up and hard reroute of the
  remaining conflicts), `clean` (final polish and exact check), `fallback` (the cleanup fallback
  runs, if needed), `write`, `check` (opens, `--drc`). `resolve` and `fallback` are skipped when
  not needed.
- `iter`: one per negotiation iteration (counted from 0, at most `iters_max`). `nets_left`: nets
  with conflicts or unrouted connections; `eta_s`: rough time to the end of the negotiation (mean
  iteration time × iterations left, capped by `--time-limit`; 0 once there are no conflicts;
  `null` if unknown). The negotiation often stops early on a plateau (`--stall-iters`), so treat
  the ETA as an upper bound.
- `done`: always the last event, also on errors (`"ok":false,"error":"…"`). `v` is the schema
  version; `stopped` is `null`, `time-limit`, `signal` or `cancel` as in `--json`.

## Benchmark (PCBench)

`scripts/bench_pcbench.py` routes eight MIT-licensed boards from the PCBench set that Freerouting
benchmarks with, end to end and without manual steps: download (pinned commit, sha256), keep the
board's own net classes (track widths, clearances, vias) and setup minimums, strip all tracks and
vias, then one `copperpath autoroute --time 120` (planes, fan-out, signals, pours) and a sign-off
with `kicad-cli pcb drc --refill-zones`. Result of the current main (4 cores, 2026-10-26):

| board | layers | nets | unconnected before → after | new DRC (KiCad) | route s | vias (human) | length mm (human) |
|---|---|---|---|---|---|---|---|
| fan_controller | 2 | 31 | 77 → **0** | 0 | 4.5 | 34 (23) | 593 (534) |
| LVDS2TMDS | 2 | 29 | 39 → **0** | 0 | 0.7 | 10 (13) | 274 (274) |
| sizif128 | 2 | 28 | 272 → 16 | starved_thermal 4 | 115 | 243 (203) | 6518 (8329) |
| rxadc_14 | 4 | 47 | 78 → 5 | solder_mask_bridge 3 | 9.5 | 78 (31) | 493 (447) |
| icehat | 4 | 59 | 104 → 10 | 0 | 52 | 61 (41) | 970 (1251) |
| rf_siggen | 4 | 57 | 153 → 16 | 0 | 15 | 175 (369) | 998 (1108) |
| a123_bcm | 4 | 139 | 92 → 1 ¹ | 0 ¹ | 6.4 | 66 (88) | 829 (1065) |
| prog_rig | 4 | 287 | 499 → 29 | 0 | 154 | 539 (332) | 9250 (12796) |

¹ kicad-cli's zone refill on a123_bcm does not finish within 600 s; the benchmark then checks
both boards with `copperpath drc --refill-zones` (about 1 s).

How much time to give `autoroute`: the same boards with `--time 10, 30, 60, 120` (x: the time
the run actually took). Smaller boards are done in about 10 s and gain nothing from more time;
the dense two-layer sizif128 needs about a minute. An agent can start with `--time 10`, look at
the open nets and spend more time only where they remain.

(a123_bcm has no earlier value: kicad-cli timed out on it before the benchmark fell back to the
native DRC.) The history per release lives in [docs/benchmark.md](docs/benchmark.md); the `Benchmark`
workflow adds a row for every release tag. Routed boards (`render --refill-zones --fills
--opens`, white lines are the remaining open connections):

| | |
|---|---|
|  |  |
|  |  |
|  |  |

DRC time on the routed boards with the saved fills, best of three: the native `drc` gives the
same violations as kicad-cli in 7-105 ms instead of 0.65-1.8 s
(`scripts/readme_figures.py` regenerates figures and chart from a benchmark run).

## Comparison with Freerouting

Freerouting is the established open-source autorouter for KiCad (via Specctra DSN). An informal
comparison on one region of a 6-layer mixed-signal board (46 nets, 90 connections, 4 threads,
same placed input):

| | copperpath | Freerouting (60 s budget) | Freerouting (full run, ~5 min) |
|---|---|---|---|
| connections routed | 90 / 90 | 83 / 90 | 81 / 90 |
| new KiCad DRC errors | 0 | clearance errors (rules not in DSN) | dangling tracks |
| wall time | 5–15 s | 50 s | ~300 s |
| vias | ~28 | 9 | 9 |

- copperpath reads the KiCad rules directly (DRU conditions such as outer-layer-only clearances
  or rule areas), so it does not lose rules in the DSN export, and it is fast and parallel.
- Freerouting uses far fewer vias, produces somewhat shorter tracks, has years of polish and
  handles many more cases (differential pairs, more board types). After its optimisation passes
  its geometry is often cleaner in open areas.
- One board is not a benchmark. Measure on your own boards (the demo is a starting point).

## Limitations

- Copper layers are indexed as a 6-layer stack (`F.Cu`, `In1..In4.Cu`, `B.Cu`); boards with more
  inner layers are not supported. Boards with fewer layers work (missing layers are masked out; tested with 4 layers).
- Plane nets, pours and high-current/HV nets are not routed (skip them via the config); existing
  zones are obstacles (locked) or ignored (unlocked or listed in `yield_pours`, refilled later by
  KiCad). Existing tracks and vias, locked or not, are kept and block other nets.
- DRU conditions that depend on position (`intersectsCourtyard`, `insideArea`) are not evaluated by
  the clearance matrix (a clearance relaxed inside a courtyard is not used); `track_width` rules
  with `intersectsCourtyard` set the neck-down width inside that courtyard (`route`, `fanout`).
- Through vias only; no differential pairs, no length tuning; DRU max-length rules are only used by
  `place`.
- Very long multi-pin nets are slow (millions of nodes per search); restrict with `--region`/`--nets`.
- Panels: every closed Edge.Cuts outline is its own board area (cut-outs inside an outline are
  holes); `--outline N` (1-based, file order) restricts any command to one outline.
- KiCad 6 or newer board files only; open and save older boards in KiCad first.
- Uses more vias than Freerouting; tune `--via-cost` and `class_layers`.
- Legality is exact at grid cell centres; off-grid pad centres are reached by stubs and verified
  exactly, but rare edge cases can still show up in KiCad DRC. Always run `--drc`.

## Scripts

| script | needs | job |
|---|---|---|
| `scripts/make_demo.py [OUT_DIR]` | KiCad 10 Python (`pcbnew`), KiCad footprint library | regenerate the demo board |
| `scripts/apply_place.py IN place.json OUT` | KiCad 10 Python (`pcbnew`) | apply a `place` result to a copy |
| `scripts/readme_figures.py --work bench_work` | Python 3, kicad-cli | README renders of the routed benchmark boards and the DRC time chart |
| `scripts/make_stress.py OUT.kicad_pcb [--parts 800] [--layers 6]` | Python 3 | synthetic stress board (SOIC-8 clusters with 0603 passives, GND/+3V3 zones) for benchmarks |
| `scripts/plot_route.py OUT.png x0,y0,x1,y1 TITLE=B.kicad_pcb ...` | Python 3, matplotlib | side-by-side copper plots |
| `scripts/drc_compare.py base.json new.json` | Python 3 | diff two kicad-cli DRC reports |
| `scripts/release.sh [--no-latest]` | bash, git, cargo | build, test, copy the binary to `$COPPERPATH_RELEASE_DIR` |

Run the `pcbnew` scripts with KiCad's bundled Python (e.g. on macOS
`/Applications/KiCad/KiCad.app/Contents/Frameworks/Python.framework/Versions/Current/bin/python3`).

## KiCad plugin

[`kicad-plugin/`](kicad-plugin/README.md) adds a **Route with copperpath** button to the KiCad
9/10 PCB editor (IPC API). It routes the open board and pushes the result as one commit, so one
Ctrl+Z undoes it and no file is reloaded. Further actions work on the selection: **Route selected
nets**, **Route region** (a rectangle on a User layer), **Rip up selected nets** and **Rip up and
reroute selected nets**. While copperpath runs, a progress dialog shows the phase, iteration,
conflicts, nets left and an ETA; the editor stays usable, and the route can be stopped (the best
result so far is applied) or cancelled and discarded.

## Contributing and issues

See [CONTRIBUTING.md](CONTRIBUTING.md). Report bad results with the "Bad routing result" issue
template and a **synthetic** repro board, never with proprietary board data.

## License

Licensed under either of

- Apache License, Version 2.0 ([LICENSE-APACHE](LICENSE-APACHE))
- MIT license ([LICENSE-MIT](LICENSE-MIT))

at your option. Unless you explicitly state otherwise, any contribution intentionally submitted
for inclusion in this work, as defined in the Apache-2.0 license, shall be dual licensed as above,
without any additional terms or conditions. Third-party licenses: [THIRD_PARTY.md](THIRD_PARTY.md).

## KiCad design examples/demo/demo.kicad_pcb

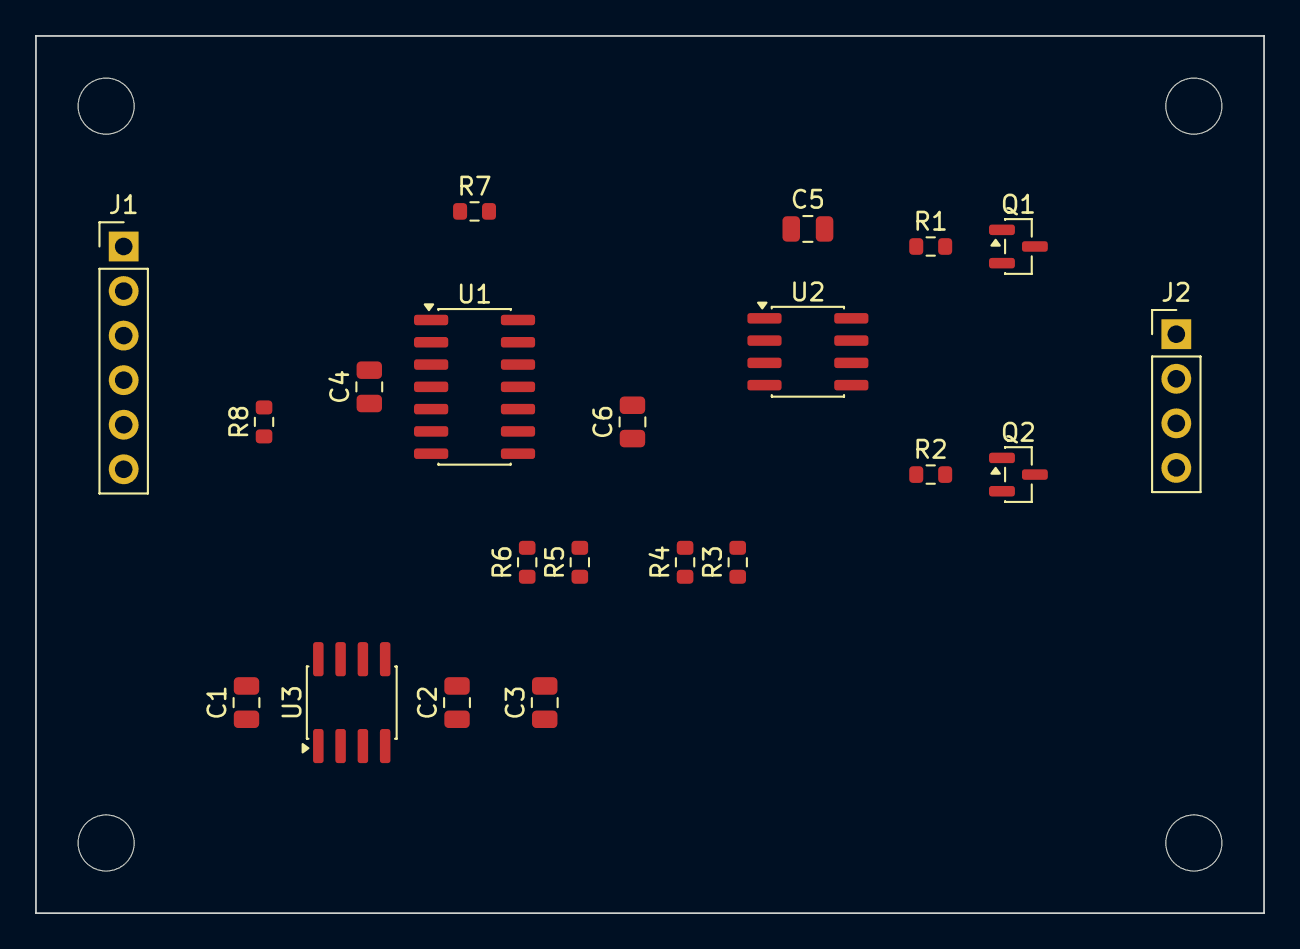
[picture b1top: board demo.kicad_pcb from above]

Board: 4 copper layers, 70.0 x 50.0 mm, 25 parts (0 on the bottom side), 24 nets, no tracks yet.

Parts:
C1, C2: 10u; C_0805_2012Metric
C3: 1u; C_0805_2012Metric
C4, C5, C6: 100n; C_0805_2012Metric
J1: Header 1x06; PinHeader_1x06_P2.54mm_Vertical
J2: Header 1x04; PinHeader_1x04_P2.54mm_Vertical
MH1, MH2, MH3, MH4: M3; MountingHole_3.2mm_M3
Q1, Q2: NMOS; SOT-23
R1, R2: 10R; R_0603_1608Metric
R3, R5, R6, R7, R8: 10k; R_0603_1608Metric
R4: 1k; R_0603_1608Metric
U1: Controller; SOIC-14_3.9x8.7mm_P1.27mm
U2: Driver; SOIC-8_3.9x4.9mm_P1.27mm
U3: Regulator; SOIC-8_3.9x4.9mm_P1.27mm

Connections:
+3V3: C3.1, C4.1, R7.1, R8.2, U1.1, U3.4
+5V: C2.1, C5.1, U2.1, U2.8, U3.3
ADC1: R3.2, R4.1, U1.9
ADC2: R5.2, R6.1, U1.10
CLK: U1.13, U3.5
DRV_A: R1.1, U2.7
DRV_A_R: Q1.1, R1.2
DRV_B: R2.1, U2.5
DRV_B_R: Q2.1, R2.2
EN: J1.5, R8.1, U1.4
FAULT: J1.6, U1.5
GND: C1.2, C2.2, C3.2, C4.2, C5.2, C6.2, J1.2, J2.3, Q1.2, Q2.2, R4.2, R6.2, U1.7, U2.4, U3.2, U3.8
LED: U1.11, U3.6
NRST: R7.2, U1.12
OUT_A: J2.1, Q1.3
OUT_B: J2.2, Q2.3
PWM_A: U1.6, U2.2
PWM_B: U1.8, U2.3
SCL: J1.4, U1.3
SDA: J1.3, U1.2
SENSE: J2.4, R3.1
SW: U2.6, U3.7
VIN: C1.1, J1.1, U3.1
VREF: C6.1, R5.1, U1.14
